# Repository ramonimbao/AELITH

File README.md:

# ÆLITH (or AELITH)

[![CC BY-NC-SA 4.0][cc-by-nc-sa-shield]][cc-by-nc-sa]

### Through-hole Alice-layout Keyboard

*Thanks to dumbothedog for the photo.*

### Partslist
 |Count|Part|
 |-|-|
 |1|ATmega32A 40 pin DIP|
 |1|40 pin DIP socket|
 |1|HRO-TYPE-C-M-12|
 |1|500 mA polyfuse|
 |2|6mm momentary push buttons|
 |1|16 MHz quarz crystal|
 |1|4.7 uF electrolytic capacitor|
 |2|100 nF ceramic disk capacitor|
 |2|22 pF ceramic disk capacitor|
 |2|68 Ω resistor|
 |2|1.5 kΩ resistor|
 |2|5.1 kΩ resistor|
 |2|3.6 V zener diode|
 |71|universal switching diode|

This work is licensed under a
[Creative Commons Attribution-NonCommercial-ShareAlike 4.0 International License][cc-by-nc-sa].

This design may be freely produced, modified, and manufactured for **PERSONAL USE ONLY** and may not be reproduced in physical form for public sale.

[![CC BY-NC-SA 4.0][cc-by-nc-sa-image]][cc-by-nc-sa]

[cc-by-nc-sa]: http://creativecommons.org/licenses/by-nc-sa/4.0/
[cc-by-nc-sa-image]: https://licensebuttons.net/l/by-nc-sa/4.0/88x31.png
[cc-by-nc-sa-shield]: https://img.shields.io/badge/License-CC%20BY--NC--SA%204.0-lightgrey.svg

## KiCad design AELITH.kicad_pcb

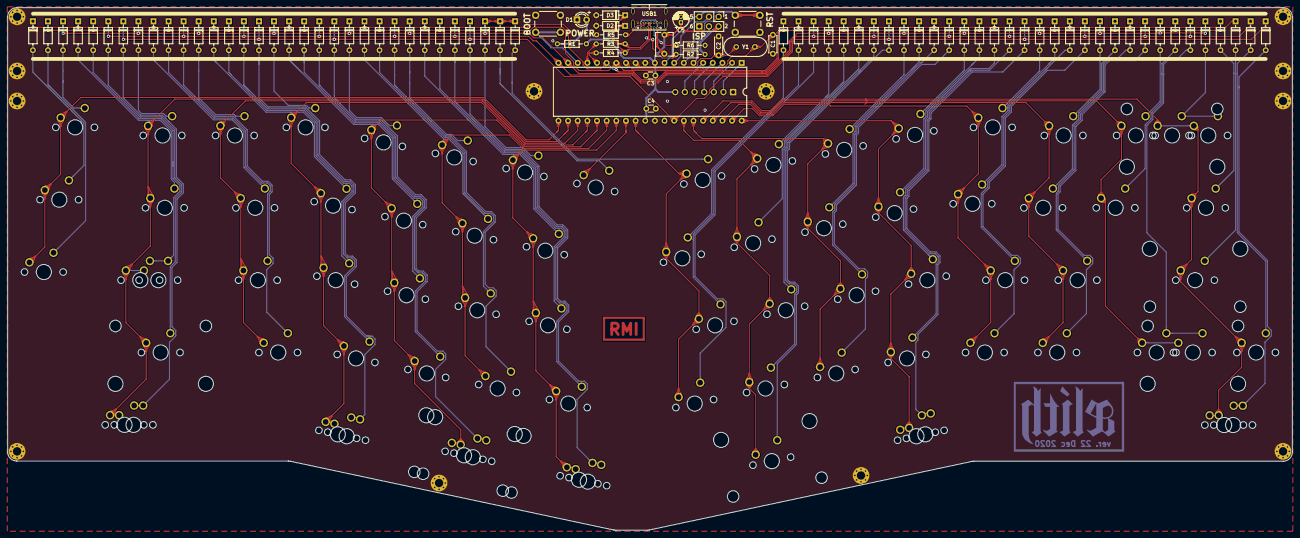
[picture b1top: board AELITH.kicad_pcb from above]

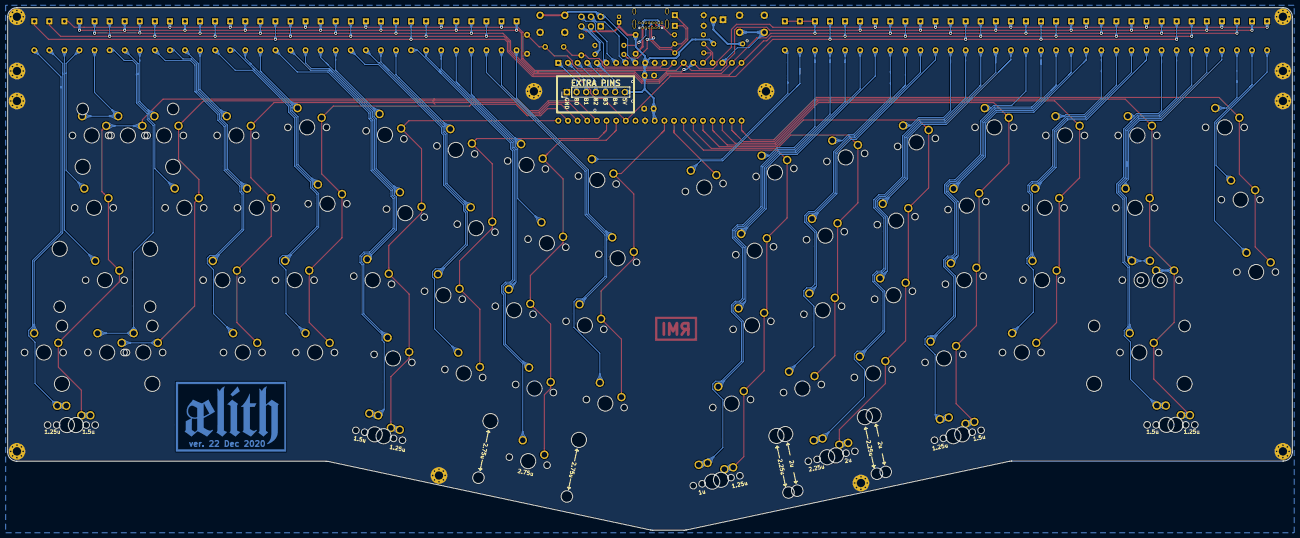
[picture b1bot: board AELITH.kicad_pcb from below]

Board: 2 copper layers, 338.3 x 137.6 mm, 177 parts (2 on the bottom side), 109 nets.

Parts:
C1, C2: 22pF; C_Disc_D4.3mm_W1.9mm_P5.00mm
C3, C4: 100nF; C_Disc_D3.0mm_W1.6mm_P2.50mm
C5: 10uF; CP_Radial_D4.0mm_P1.50mm
D1: LED; LED_D3.0mm
D2, D3: 3.6V; D_DO-35_SOD27_P7.62mm_Horizontal
D4, D5, D6, D7, D8, D9, D10, D11, D12, D13, D14, D15, D16, D17, D18, D19, D20, D21, D22, D23, D24, D25, D26, D28, D29, D30, D31, D32, D33, D34, D35, D36, D37, D38, D39, D40, D41, D42, D44, D45, D46, D47, D48, D49, D51, D52, D53, D54, D55, D56, D57, D59, D60, D61, D62, D63, D64, D65, D66, D67, D68, D69, D70, D71, D72, D73: 1N4148; D_DO-35_SOD27_P7.62mm_Horizontal
F1: 500mA; C_Disc_D6.0mm_W4.4mm_P5.00mm
G1: Signature
G2: Logo; AELITH_Logo
H1, H2, H3, H4, H5, H6, H7, H8, H9, H10, H11, H12: M2; MountingHole_2.2mm_M2_Pad_Via
J1: Conn_02x03_Odd_Even; PinHeader_2x03_P2.54mm_Vertical
J2: Conn_01x07; PinHeader_1x07_P2.54mm_Vertical
MX1, MX2, MX3, MX4, MX5, MX6, MX7, MX8, MX9, MX10, MX11, MX12, MX13, MX14, MX15, MX16, MX18, MX20, MX21, MX22, MX23, MX24, MX26, MX27, MX28, MX29, MX30, MX31, MX32, MX34, MX36, MX37, MX38, MX39, MX40, MX42, MX43, MX44, MX45, MX46, MX47, MX52, MX53, MX54, MX55, MX56, MX58, MX59, MX60, MX61, MX62, MX63, MX65, MX77: MX-LED; MXOnly-1U-NoLED
MX17: MX-LED; MXOnly-2U-NoLED
MX19, MX33, MX67, MX68, MX72, MX73: MX-LED; MXOnly-1.5U-NoLED
MX35, MX64: MX-LED; MXOnly-1.75U-NoLED
MX49, MX76: MX-LED; MXOnly-2.25U-ReversedStabilizers-NoLED
MX50, MX70, MX74, MX75, MX78, MX79: MX-LED; MXOnly-1.25U-NoLED
MX51: MX-LED; MXOnly-2.25U-NoLED
MX66: MX-LED; MXOnly-2.75U-NoLED
MX69: MX-LED; MXOnly-2U-ReversedStabilizers-NoLED
MX71: MX-LED; MXOnly-2.75U-ReversedStabilizers-NoLED
R1, R2: 1.5k; R_Axial_DIN0204_L3.6mm_D1.6mm_P7.62mm_Horizontal
R3, R4: 75; R_Axial_DIN0204_L3.6mm_D1.6mm_P7.62mm_Horizontal
R5, R6: 5.1k; R_Axial_DIN0204_L3.6mm_D1.6mm_P7.62mm_Horizontal
SW1, SW2: SW_Push; SW_PUSH_6mm
U1: ATmega32A-PU; DIP-40_W15.24mm
USB1: USB_C_Receptacle_USB2.0; USB_C_GCT_USB4085
Y1: 16MHz; Crystal_HC49-4H_Vertical

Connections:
+5V: C3.1, C4.1, C5.1, F1.1, J1.2, J2.7, R1.2, R2.2, U1.10, U1.30
/A0: MX12.1, MX29.1, MX45.1, MX61.1, MX72.1, MX78.1, U1.40
/A1: MX13.1, MX30.1, MX46.1, MX62.1, U1.39
/A2: MX14.1, MX31.1, MX47.1, MX63.1, U1.38
/A3: MX15.1, MX32.1, MX64.1, MX66.1, U1.37
/A4: MX16.1, MX17.1, MX33.1, MX49.1, MX65.1, MX73.1, MX79.1, U1.36
/A5: MX11.1, MX28.1, MX44.1, MX60.1, U1.35
/A6: MX10.1, MX27.1, MX43.1, MX59.1, MX71.1, U1.34
/A7: D67.1, D68.1, D69.1, D70.1, D71.1, D72.1, D73.1, U1.33
/B0: J2.2, U1.1
/B1: J2.3, U1.2
/B2: J2.4, U1.3
/B3: J2.5, U1.4
/B4: J2.6, U1.5
/BOOT: SW2.1, U1.18
/C0: MX2.1, MX19.1, MX35.1, MX50.1, MX51.1, MX67.1, MX74.1, U1.22
/C1: MX3.1, MX20.1, MX36.1, MX52.1, U1.23
/C2: MX4.1, MX21.1, MX37.1, MX53.1, MX68.1, MX75.1, U1.24
/C3: MX5.1, MX22.1, MX38.1, MX54.1, MX69.1, MX76.1, U1.25
/C4: MX6.1, MX23.1, MX39.1, MX55.1, U1.26
/C5: MX7.1, MX24.1, MX40.1, MX56.1, MX70.1, MX77.1, U1.27
/C6: MX8.1, U1.28
/C7: MX9.1, MX26.1, MX42.1, MX58.1, U1.29
/D0: D36.1, D37.1, D38.1, D39.1, D40.1, D41.1, D42.1, D44.1, D45.1, D46.1, D47.1, D48.1, D49.1, D51.1, U1.14
/D1: D20.1, D21.1, D22.1, D23.1, D24.1, D25.1, D26.1, D28.1, D29.1, D30.1, D31.1, D32.1, D33.1, D34.1, D35.1, U1.15
/D5: D4.1, D5.1, D6.1, D7.1, D8.1, D9.1, D10.1, D11.1, D12.1, D13.1, D14.1, D15.1, D16.1, D17.1, D18.1, D19.1, U1.19
/D6: D52.1, D53.1, D54.1, D55.1, D56.1, D57.1, D59.1, D60.1, D61.1, D62.1, D63.1, D64.1, D65.1, D66.1, U1.20
/D7: MX1.1, MX18.1, MX34.1, U1.21
/DBUS+: D3.1, R4.1, USB1.A6, USB1.B6
/DBUS-: D2.1, R2.1, R3.1, USB1.A7, USB1.B7
D+: R4.2, U1.16
D-: R3.2, U1.17
GND: C1.2, C2.1, C3.2, C4.2, C5.2, D1.1, D2.2, D3.2, H1.1, H2.1, H3.1, H4.1, H5.1, H6.1, H7.1, H8.1, H9.1, H10.1, H11.1, H12.1, J1.6, J2.1, R5.1, R6.2, SW1.1, SW2.2, U1.11, U1.31, USB1.B1, USB1.B12, USB1.S1
MISO: J1.1, U1.7
MOSI: J1.4, U1.6
NRST: J1.5, SW1.2, U1.9
unnamed: C1.1, U1.13, Y1.1
unnamed: C2.2, U1.12, Y1.2
unnamed: D1.2, R1.1
unnamed: D4.2, MX1.2
unnamed: D5.2, MX2.2
unnamed: D6.2, MX3.2
unnamed: D7.2, MX4.2
unnamed: D8.2, MX5.2
unnamed: D9.2, MX6.2
unnamed: D10.2, MX7.2
unnamed: D11.2, MX8.2
unnamed: D12.2, MX9.2
unnamed: D13.2, MX10.2
unnamed: D14.2, MX11.2
unnamed: D15.2, MX12.2
unnamed: D16.2, MX13.2
unnamed: D17.2, MX14.2
unnamed: D18.2, MX15.2
unnamed: D19.2, MX16.2, MX17.2
unnamed: D20.2, MX18.2
unnamed: D21.2, MX19.2
unnamed: D22.2, MX20.2
unnamed: D23.2, MX21.2
unnamed: D24.2, MX22.2
unnamed: D25.2, MX23.2
unnamed: D26.2, MX24.2
unnamed: D28.2, MX26.2
unnamed: D29.2, MX27.2
unnamed: D30.2, MX28.2
unnamed: D31.2, MX29.2
unnamed: D32.2, MX30.2
unnamed: D33.2, MX31.2
unnamed: D34.2, MX32.2
unnamed: D35.2, MX33.2
unnamed: D36.2, MX34.2
unnamed: D37.2, MX35.2, MX50.2
unnamed: D38.2, MX36.2
unnamed: D39.2, MX37.2
unnamed: D40.2, MX38.2
unnamed: D41.2, MX39.2
unnamed: D42.2, MX40.2
unnamed: D44.2, MX42.2
unnamed: D45.2, MX43.2
unnamed: D46.2, MX44.2
unnamed: D47.2, MX45.2
unnamed: D48.2, MX46.2
unnamed: D49.2, MX47.2
unnamed: D51.2, MX49.2
unnamed: D52.2, MX51.2
unnamed: D53.2, MX52.2
unnamed: D54.2, MX53.2
unnamed: D55.2, MX54.2
unnamed: D56.2, MX55.2
unnamed: D57.2, MX56.2
unnamed: D59.2, MX58.2
unnamed: D60.2, MX59.2
unnamed: D61.2, MX60.2
unnamed: D62.2, MX61.2
unnamed: D63.2, MX62.2
unnamed: D64.2, MX63.2
unnamed: D65.2, MX64.2, MX66.2
unnamed: D66.2, MX65.2
unnamed: D67.2, MX67.2, MX74.2
unnamed: D68.2, MX68.2, MX75.2
unnamed: D69.2, MX69.2, MX76.2
unnamed: D70.2, MX70.2, MX77.2
unnamed: D71.2, MX71.2
unnamed: D72.2, MX72.2, MX78.2
unnamed: D73.2, MX73.2, MX79.2
unnamed: R5.2, USB1.B5
unnamed: R6.1, USB1.A5
SCLK: J1.3, U1.8
VBUS: F1.2, USB1.A4, USB1.A9, USB1.B4, USB1.B9

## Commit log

2021-10-06 Add image credit
